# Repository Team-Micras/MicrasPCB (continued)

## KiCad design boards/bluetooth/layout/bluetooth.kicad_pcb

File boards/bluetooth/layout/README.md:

# Bluetooth module

The Micras Bluetooth module: a 16 x 25 mm, 2-layer, 0.79 mm board with an HM-19 Bluetooth Low
Energy module (TI CC2640R2F) and a vertical USB-C plug. It plugs into the main board's USB-C
receptacle U2 and stands upright behind the robot, and gives the firmware a wireless UART
(MicrasFirmware `bluetooth_design.md`: UART4, 115 200 8N1, no flow control). The main board it
plugs into is the v1 main board (MicrasPCB e34fb9a, `boards/main`); the current main board has no
USB-C receptacle, and its ESP32-C5 takes the radio's role.

The circuit is the MicrasBluetoothModule Altium design with two changes from the design review
(`hw_debug/schematic_review.md`): the plug's CC contacts carry the module's signature (M6), and
R4 pulls the HM-19's RESETB up (m17). Every part keeps its designator, and `micras-pcb previous
compare bluetooth` checks the netlist against that design's connectivity
([`previous/board.json`](../previous/board.json)) plus the changes in
[`changes.toml`](../changes.toml).

## Files

The board files are in `boards/bluetooth/` (this README sits in its `layout/` folder);
`spec/` is at the repository root.

| File | Contents |
|---|---|
| [`bluetooth.zen`](../bluetooth.zen) | the circuit (U1 HM-19, USB1 plug, R1-R4, C1, C2, D1, OP1), board stackup and rules |
| [`schematic/`](../schematic) | how the sheet is drawn (`micras-pcb sch`): the plug, and the HM-19 with its application circuit |
| [`erc.toml`](../erc.toml) | 3V3 and GND come from the main board through the plug (the PWR_FLAG role for ERC) |
| [`changes.toml`](../changes.toml) | connectivity changes against the previous revision: the CC signature (M6), the RESETB pull-up (m17) |
| [`test/`](../test) | `pcb test` bench of the circuit: HM-19 application circuit, LED current, USB-C signature, SBU and VBUS, RESETB |
| [`layout/`](.) | this folder: the KiCad project; the `.kicad_pcb` holds placement and routing; [`fixes.py`](fixes.py) is the pcbnew script that made the review fixes in it |
| [`previous/`](../previous) | the previous revision's snapshot and [`transfer_layout.py`](../previous/transfer_layout.py), which builds the layout from it |
| [`spec/bluetooth.toml`](../../../spec/bluetooth.toml) | mechanics: thickness, outline extents, plug and HM-19 positions, mating with the main board's U2 |

`tests/test_bluetooth.py` checks the board against its previous revision and the spec; the v1 main
board's tests (e34fb9a) check the joint with it.

## Circuit

The HM-19 application circuit of its datasheet (JNHuaMao "HM Bluetooth module datasheet" V107,
section 6.5); the docstring of [`bluetooth.zen`](../bluetooth.zen) cites each value.

| Part | Function |
|---|---|
| U1 | HM-19, VCC 2.1-3.7 V (V107 section 3), pins 9 and 10 on 3V3 |
| C1, C2 | 10 uF 35 V X5R and 100 nF 50 V X7R on 3V3 |
| R1 | 1 kOhm from HM-19 UART_TX (pin 2) to the plug's D- contacts (net `UART_TX`) |
| R2 | 1 kOhm from HM-19 UART_RX (pin 4) to the plug's D+ contacts (net `UART_RX`) |
| R3, D1 | the "System LED" output PIO1 (pin 15) through 680 Ohm to a blue 0603 LED: about 0.6 mA |
| R4 | 10 kOhm from RESETB (pin 11) to 3V3: the CC2640R2F's RESET_N has no internal pull-up (SWRS204C Table 7-1) |
| OP1 | open pad (bottom side) from PIO0 (pin 16, the key) to GND |
| USB1 | USB-C plug: 3V3 on SBU1/SBU2, UART on D+/D-, GND, CC1 and CC2 on D+ (the signature); VBUS open |

RTS, CTS, KEY (pin 8), PIO2 and PIO3 are open, as in the vendor schematic.

## Interface with the main board

The plug mates the main board's U2 (GT-USB-7010ASV) contact by contact. The plug joins both D+
contacts, both D- contacts and SBU1 with SBU2, and U2 joins them the same way, so the module works
either side up (the v1 main board's `tests/test_bluetooth.py` checks both orientations).

| Contacts | Module | Main board |
|---|---|---|
| SBU1, SBU2 (A8, B8) | `3V3`: U1 VCC, C1, C2 | `PERIPHERALS.SBU_PWR`: 3V3 through a switch and the PTC fuse F1 (KASML010), on while the main board reads the signature |
| D- (A7, B7) | `UART_TX`: R1 from HM-19 UART_TX | to MCU PA11 = UART4_RX |
| D+ (A6, B6) | `UART_RX`: R2 to HM-19 UART_RX | from MCU PA12 = UART4_TX |
| CC1, CC2 (A5, B5) | `UART_RX` (the signature) | R6, R7 5.1 kOhm Rd to GND, and the signature detector |
| GND, shell | `GND` | `GND` |
| VBUS (A4, A9, B4, B9) | open | `+5V`, the main board's USB power input |

The UART crosses correctly: the module transmits on D- into the MCU's receiver PA11, and receives
on D+ from PA12. With 1 kOhm in series per line on the module, the RC with the main board's
D+/D- capacitance (tens of pF) is tens of ns, against 8.68 us per bit at 115 200 baud.

### The signature (review M6)

USB Type-C reserves SBU for specified uses: a port leaves it open or pulls it down by at least
950 kOhm (Type-C R2.0 section 4.3 p139, Table 4-28 p236), and a full-featured cable wires it
through to a host's Alternate Mode or an audio accessory's microphone. So the main board may put
3V3 on SBU only when the module, and nothing else, is in its receptacle. The module identifies
itself on CC:

- **Module.** Both CC contacts are on its D+ contacts, so the signature shows either side up.
- **Main board.** D+ is the MCU's UART4 TX (PA12), which idles high once the firmware has started
  UART4 (at boot, `MX_UART4_Init`). Through the module it pulls the main board's CC contacts,
  each 5.1 kOhm Rd to GND, to the TX level: about 3.2 V, at least 2.87 V (STM32H725 DS13311
  Table 56: VOH >= VDD - 0.4 V; 3V3 >= 3.27 V). No Type-C partner makes that: across a sink's Rd
  a source makes at most 2.04 V (Table 4-36, vRd-Connect, +-10 % Rd; 2.18 V with +-20 %,
  Table 4-35), and cables and accessories only add Ra or Rd to GND. The main board's detector
  holds the peak of its CC1 through the UART's low bits and switches 3V3 onto SBU through F1
  when that peak rises above 2.26 V (two thirds of 3V3), and off again below 2.06 V. Its Rd stays
  as it is, so it is still a USB Type-C sink and its USB power input is unchanged.
- **Cost.** PA12 drives the two Rd in parallel, 2.55 kOhm (1.3 mA), while the module is plugged
  in. The module is unpowered until the firmware starts UART4, and loses power about 0.3 s after
  PA12 stops driving (an MCU reset held that long), as the detector's hold decays. Until the
  detector switches on (about 15 ms), PA12 also feeds a little current into the unpowered HM-19's
  UART_RX pin through R2.
- **Elsewhere.** Plugged into another USB-C port the module gets no supply (its VBUS is open and
  a host never drives SBU) and does nothing.

The main board's side is in its own pull request (the review fixes, #13).

## Board

2 copper layers, 35 um copper on a 0.7 mm FR-4 core (Dk 4.5), from the Altium layer stack; with
Zener's fixed 10 um solder mask a side it is 0.79 mm (Altium's 12.7 um resist makes 0.7954 mm),
ordered as JLCPCB's 0.8 mm board. Design rules: 0.1 mm clearance, 0.254 mm track, 0.6 / 0.3 mm
and 0.5 / 0.3 mm vias, 0.2 mm copper to edge, 0.02 mm solder mask expansion, the Altium JLCPCB
rule set; `rules/jlcpcb.kicad_dru` adds JLCPCB's limits on top. ENIG finish, black solder mask
and white silkscreen (Zener's 2-layer defaults, the owner's choice).

## Layout

The layout is the Altium MicrasBluetoothModule.PcbDoc's, in the same KiCad coordinates, built by
[`previous/transfer_layout.py`](../previous/transfer_layout.py) from KiCad's conversion of that PCB
(running the script again changes nothing), with the review fixes made on it by
[`layout/fixes.py`](fixes.py), which also sets the designators' size.

- **Top**: U1 near the top edge, with the antenna end of the module (the 7 mm above pad 1, V107
  6.6) 5.5 mm beyond the board's top edge; R2, R1, R3, D1, C2, C1 in a row below it, R4 above C2;
  USB1 at the bottom, in the narrow neck, with its CC pads joined to the adjacent D+ pads. RESETB
  runs from R4 under the module to U1 pad 11 from the inside of the pad row. GND pour.
- **Bottom**: OP1 at the top, the MICRAS logo in silkscreen, the routing that crosses the plug's
  rows. GND pour.
- The outline narrows from 16 mm to the plug's width towards the bottom edge.
- Resistors, capacitors and D1 use KiCad's generic footprints, each centred on its pads' positions
  in the Altium footprint: pad centres within 75 um of the Altium ones (the 0603 pad pitches
  differ). D1 carries KiCad's LED model scaled to the SMLD12BN1W's 0.55 mm height (ROHM
  datasheet p. 1). The teardrops of the Altium design are plain copper zones (priorities 100 and
  up), as on the main board: KiCad 10 orders zones by UUID and does not save a teardrop's UUID.
  They fill with a 0.1 mm minimum width, JLCPCB's minimum copper feature.
- The GND pours keep the Altium polygons' neck widths (copper narrower than 0.1 mm, 0.3 mm in the
  top pour around the plug, is not poured) and join pads solidly.
- The Edge.Cuts outline is the Altium one without its seven duplicated vertices (lines of 1-12 nm,
  which KiCad reads as a malformed, self-intersecting outline); the lines next to them meet within
  12 nm of where they did.
- Silkscreen: the reference designators are 0.5 mm high with a 0.125 mm stroke (the owner's
  choice), and so is the board's minimum (`bluetooth.zen`, `Silkscreen(minimum_text_height=0.5)`;
  the stroke in `rules/kicad-severities.toml`). JLCPCB recommends 1.0 mm text, so these may print
  less sharply; that is accepted.

## Differences from the Altium board

There is no Gerber output of the Altium design to compare with; against KiCad's conversion of the
PcbDoc, the board differs, besides the review fixes (the CC signature tracks, R4 and its tracks,
C2's designator beside C2), in:

| What | This board | Altium board | Why |
|---|---|---|---|
| Pour to board edge | 0.21 mm | 0.23 mm | the KiCad fill under `rules/jlcpcb.kicad_dru`: JLCPCB's 0.2 mm routed-edge clearance plus 10 um for the fill's arc approximation |
| R1-R3, C1, C2, D1 | KiCad's generic 0603 footprints: pads R 0.80 x 0.95, C 0.90 x 0.95, LED 0.875 x 0.95 mm, their centres within 75 um of the Altium ones; KiCad's silkscreen (no box around the parts, 6.2 mm2 less ink; D1's polarity mark an outline closed on the cathode side) | pads R 0.85 x 1.0, C 0.8 x 0.9, LED 0.8 x 0.8 mm; full boxes, a triangle on D1 | the stdlib generics' footprints |
| Passive 3D models | KiCad library models: R 0.45 mm tall, C 0.8 mm wide; D1 0.55 mm | R 0.56 mm, C 0.9 mm wide, D1 0.6 mm | KiCad's generic models (D1 scaled to its datasheet) |
| U1, USB1 courtyards | F.CrtYd rectangles 0.25 mm around the HM-19 body and pads, and around the plug's pads and legs | none (the HM-19 outline on User.15) | KiCad's courtyard overlap check |
| Teardrop cusps | thinner than 0.1 mm left out | drawn to a point | JLCPCB's 0.1 mm minimum copper feature |
| Solder mask thickness | 10 um a side | 12.7 um | Zener's stackup has no mask thickness setting |

## Mechanics

[`spec/bluetooth.toml`](../../../spec/bluetooth.toml) places the board frame on the plug centre and
exports `build/bluetooth/bluetooth_mech.json` (outline polygon, plug, HM-19, and where the board
sits in the robot). Mated, the module's component side faces the main board's rear edge at the USB
notch: the plug axis is on U2's axis (robot y = -1.75 mm) at 1.68 mm above the main board's top
surface (U2 drawing, CH), and the component side at robot x = -35.60 mm, 1.5 mm behind the notch
edge (x = -34.1 mm). That x follows from the receptacle drawing's mated dimensions (6.65 mm plug
shell, 1.85 mm Ref from the plug overmold to the receptacle face) and the plug's 8.65 mm height.

## Known faults

Every gate passes (the joint's checks, its signature detector `usb_c_sbu_open` and PA11's firmware
pull-up, are the v1 main board's, at e34fb9a). DRC and layout-check report one warning:

| Check (gate) | Fault | Requirement | Fix |
|---|---|---|---|
| `copper_sliver` (drc, warning) | 1: a teardrop outline overrunning its track on F.Cu; the teardrops are plain zones, which KiCad does not exempt from the sliver test | no copper sliver | trim the outline |

Requirements without a check, and why:

- The key (m17): the HM-19 datasheet puts the system key on pin 8 in its pin table and on PIO0
  (pin 16, where OP1 is) in its schematic and AT commands. Bridging OP1 for over 1000 ms in
  standby restores the factory settings, which the firmware's AT set-up relies on; `AT+SYSK0`
  makes the key only cancel, so send it when setting the module up. Which pin the fitted module
  uses needs a bench test.
- F1 against the module current (m17): F1 holds 50 mA at 85 C (KASML010), the HM-19 datasheet
  quotes 50 mA; no source gives the temperature inside the robot. At 50 mA the module still gets
  over 3.1 V: 3.27 V minimum, F1 up to 2 Ohm (0.1 V), the switch and contacts under 15 mV,
  against its 2.1 V minimum (V107 section 3).
- Hot plugging: C1 (10 uF) charges from the main board's 3V3 through F1 when the switch turns on
  and can dip 3V3; plug the module with the power off.
- Decoupling distance: the vendor schematic gives no distance for C1/C2.
- Mated depth: derived from the receptacle drawing, not measured.

## Open items

- [ ] Check every part's placement rotation in JLCPCB's assembly preview, then set
      `rotation_verified = true` in `parts/jlc.toml`.
- [ ] The HM-19 (LCSC C9900145630) has no stock at JLCPCB: source and consign it.
- [ ] Measure the mated position on the robot and correct `spec/bluetooth.toml` [mating].
- [ ] Bench test: the main board switches SBU on with the module in either orientation, and
      off with a USB host, a C-to-C cable and an audio adapter.

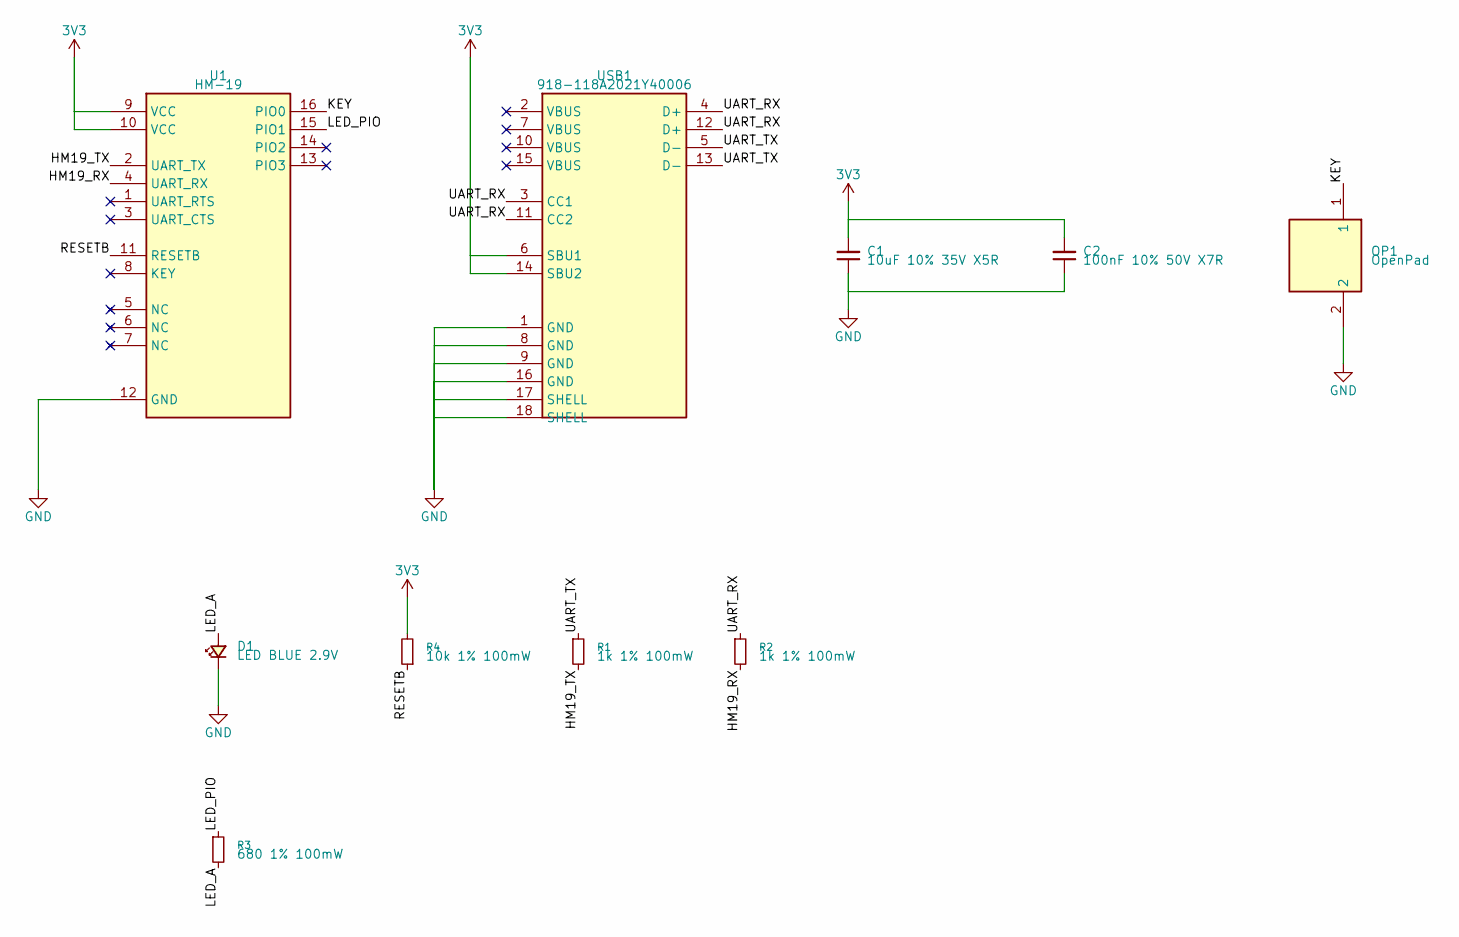
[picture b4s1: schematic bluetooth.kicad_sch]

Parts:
C1: 10uF 10% 35V X5R; C_0603_1608Metric
C2: 100nF 10% 50V X7R; C_0603_1608Metric
D1: LED BLUE 2.9V; LED_0603_1608Metric
OP1: OpenPad
R1, R2: 1k 1% 100mW; R_0603_1608Metric
R3: 680 1% 100mW; R_0603_1608Metric
R4: 10k 1% 100mW; R_0603_1608Metric
U1: HM-19
USB1: 918-118A2021Y40006; USB-C-SMD_918-118A2021Y40006

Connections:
3V3: C1.2, C2.2, R4.2, U1.9 (VCC), U1.10 (VCC), USB1.6 (SBU1), USB1.14 (SBU2)
GND: C1.1, C2.1, D1.1 (K), OP1.2, U1.12 (GND), USB1.1 (GND), USB1.8 (GND), USB1.9 (GND), USB1.16 (GND), USB1.17 (SHELL), USB1.18 (SHELL)
HM19_RX: R2.2, U1.4 (UART_RX)
HM19_TX: R1.2, U1.2 (UART_TX)
KEY: OP1.1, U1.16 (PIO0)
LED_A: D1.2 (A), R3.2
LED_PIO: R3.1, U1.15 (PIO1)
RESETB: R4.1, U1.11 (RESETB)
U1.NC_HM19_KEY: U1.8 (KEY)
U1.NC_HM19_PIO2: U1.14 (PIO2)
U1.NC_HM19_PIO3: U1.13 (PIO3)
U1.NC_HM19_UART_CTS: U1.3 (UART_CTS)
U1.NC_HM19_UART_RTS: U1.1 (UART_RTS)
UART_RX: R2.1, USB1.3 (CC1), USB1.4 (D+), USB1.11 (CC2), USB1.12 (D+)
UART_TX: R1.1, USB1.5 (D-), USB1.13 (D-)

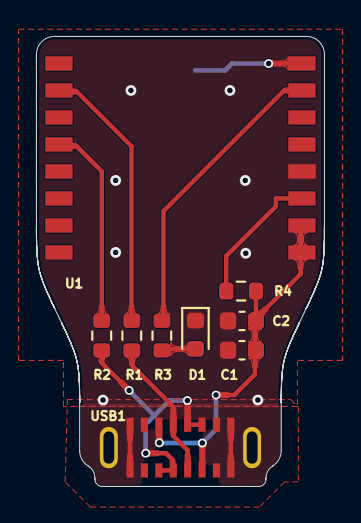
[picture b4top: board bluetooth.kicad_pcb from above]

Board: 2 copper layers, 16.0 x 25.0 mm, 10 parts (1 on the bottom side), 10 nets.

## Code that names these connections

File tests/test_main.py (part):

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    # SWD1 (main.zen): pad 1 NRST for the probe's RST wire, then the owner's clone ST-Link lead on
    # pads 2-5: 2 SWDIO, 3 GND, 4 SWCLK, 5 its 5 V pin. main.zen's docstring gives what each misplug
    # of the lead does; where the probe's 5 V lands must stay what it says.
    want = {1: d.net(MCU, "NRST"), 2: d.net(MCU, "PA13"), 3: "GND", 4: d.net(MCU, "PA14"), 5: "5V_IN"}
    got = {pad: d.net("SWD1", str(pad)) for pad in want}
    assert got == want, f"SWD1 pads {got}, expected {want}"
    lead = ["SWDIO", "GND", "SWCLK", "5V"]  # the lead's contacts in order
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
def test_no_usb_supply_and_no_5v_rail(d):
    # Research Design basis: the board has no USB receptacle and no 5 V rail; every supply comes
    # from J1. The one 5 V net is 5V_IN, a programmer's 5 V pin into VSYS through D17, which feeds
    # nothing else. The only USB nets are the ESP32-C5's data pair (GPIO13 D-, GPIO14 D+) to the bare
    # pads J3, with no VBUS (Esp.zen, USB pads).
    usb = sorted(n for n in d.nets() if re.search(r"USB|VBUS|5V", n.upper()) and n != "5V_IN")
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

def test_battery_divider_matches_the_firmware(d):
    # PC5 reads VBAT through the divider; the firmware's constant must be its ratio.
    tap = d.net(MCU, "PC5")
    vbat = d.net("IC8", "VM")
    up = d.two_terminal("resistor", vbat, tap)
    down = d.two_terminal("resistor", tap, "GND")
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# Firmware rules the hardware does not enforce (behaviour key -> words it must name).
FIRMWARE_RULES = {
    # a debug halt: the timers freeze and the drive enables drop (Drivers.zen, R49 covers reset only);
    # Motors_Enable (PD2) and Fan_Enable (PB12): one GPIOD and one GPIOB write
    "debug_halt": ["TIM1", "TIM8", "TIM14", "Motors_Enable", "Fan_Enable", "GPIOB_BSRR"],
    # the IMU shares SPI_SCK/SPI_MOSI with the encoders and decodes them as I2C while deselected
    "imu_interface": ["I2C_I3C_disable", "IF_CFG"],
    # Wall_Emitter_Set runs beside LED_ARGB and the encoder chip selects (Sensors.zen); the buzzer's
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    "emitter_slot_quiet": ["LED_ARGB", "SPI_SCK", "Encoder_Right_CSn", "Encoder_Left_CSn", "Buzzer"],
    # the STSPIN958's TOFF is low during the limiter's decay (DS14341 section 5.6.2, Figure 14), read
    # in step with the PWM; it leaves the decay only on a PWM1 low edge (section 5.6.2.2)
    "fan_toff": ["low while the limiter decays", "TIM14 has no DMA request", "GPIOB_IDR"],
    "fan_pwm": ["1 - 280 ns x fPWM", "88.8 %"],
    # the overcurrent trip is per MOSFET, so a 400 kHz stall below it persists (DS14341 section 5.7)
    "fan_start": ["per MOSFET", "12.8-28 A"],
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    # the IMU and encoder bus on SPI2 and its DMA requests (sensor_bus)
    "sensor_bus_dma": ["SPI2", "39", "40"],
    # Button's EXTI line has its interrupt to itself (button)
    "button_input": ["PC4", "EXTI4"],
    # the LEDs' timer and DMA request, the buzzer's timer (leds, buzzer; RM0468 Table 118)
    "led_timer": ["TIM15", "tim15_up", "106", "MOE"],
    "buzzer_timer": ["TIM17", "MOE"],
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        "WR_DONE (CMD7)",
        "CMD8",
        # ESP_Flow's EXTI11 shares the EXTI15_10 interrupt with Fan_Enable's fault line (EXTI12)
        "EXTI11 on PA11",
        "EXTI15_10",
    ],
    # the C5 recovers the link after the MCU resets, closing buffers with commands, not ESP_CSn
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    # Without an HSE crystal the H7 runs on its HSI, +-1 % over temperature (DS13311 Rev 5 Table 40),
    # which scales the gyro's yaw integral; the firmware then measures it against the ESP32-C5's
    # crystal over the link (firmware_changes.toml timebase), and the C5 stays on in contest mode.
    osc = [d.net(MCU, pin) for pin in ("PH0-OSC_IN", "PH1-OSC_OUT")]
    assert all(osc), f"PH0/PH1 not found on {MCU}"
    clocked = sorted(r for net in osc for r in d.refs_on(net) if d.kind(r) in CLOCK_KINDS)
    if clocked:
        pytest.skip(f"the MCU has its own clock reference: {clocked}")
    words = ["HSI", "ESP_CSn", "crystal", "loop_time", "contest"]
    text = FW["behaviour"].get("timebase", "")
    missing = [w for w in words if w not in text]
    assert not missing, f"no crystal on PH0/PH1 ({osc}): behaviour.timebase must name {missing}"


def test_every_free_running_timer_output_has_low_output_speed():
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
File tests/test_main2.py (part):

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    if vsys not in _reach(edges, vbat):
        problems.append(f"{vbat} does not reach VSYS")
    if vsys not in _reach(edges, v5):
        problems.append(f"{v5} (J2 pin 2) does not reach VSYS")
    if d.net("SWD1", "4") != v5:
        problems.append(f"SWD1 pad 4 is on {d.net('SWD1', '4')}, not J2 pin 2's {v5}")
    for start in (vbat, vsys):
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def test_swd_header_follows_the_clone_st_link_order(d):
    # The owner's clone ST-Link lead (main2.zen): pads 1 SWDIO, 2 GND, 3 SWCLK, 4 its 5 V pin. Plugged
    # turned round, or shifted one pad either way, the probe's 5 V pin never lands on GND.
    want = {1: d.net(MCU, "PA13"), 2: "GND", 3: d.net(MCU, "PA14"), 4: "5V_IN"}
    got = {pad: d.net("SWD1", str(pad)) for pad in want}
    assert got == want, f"SWD1 pads {got}, expected {want}"
    probe_5v = 4  # the lead's pins in the same order: 1 SWDIO, 2 GND, 3 SWCLK, 4 5V
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
def test_no_usb_and_no_5v_rail(d):
    # Research Design basis: the board has no USB and no 5 V rail; every supply comes from J1. The
    # one 5 V net is 5V_IN, a programmer's 5 V pin into VSYS through D17, which feeds nothing else.
    usb = sorted(n for n in d.nets() if re.search(r"USB|VBUS|5V", n.upper()) and n != "5V_IN")
    assert not usb, f"USB or 5 V nets on the board: {usb}"
    on_5v = sorted(r for r, _, _ in d.on("5V_IN"))
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

def test_battery_divider_matches_the_firmware(d):
    # PC5 reads VBAT through the divider; the firmware's constant must be its ratio.
    tap = d.net(MCU, "PC5")
    vbat = d.net("IC8", "VM")
    up = d.two_terminal("resistor", vbat, tap)
    down = d.two_terminal("resistor", tap, "GND")
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# Firmware rules the hardware does not enforce (behaviour key -> words it must name).
FIRMWARE_RULES = {
    # a debug halt: the timers freeze and the drive enables drop (Drivers.zen, R49 covers reset only);
    # Motors_Enable (PB8) and Fan_Enable (PB12) are both port B pins: one GPIOB write
    "debug_halt": ["TIM1", "TIM8", "TIM14", "Motors_Enable", "Fan_Enable", "GPIOB_BSRR"],
    # the IMU shares SPI_SCK/SPI_MOSI with the encoders and decodes them as I2C while deselected
    "imu_interface": ["I2C_I3C_disable", "IF_CFG"],
    # Wall_Emitter_Set runs beside LED_ARGB and the encoder chip selects (Sensors.zen)
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    # the IMU and encoder bus on SPI2 and its DMA requests (sensor_bus)
    "sensor_bus_dma": ["SPI2", "39", "40"],
    # Button's EXTI line has its interrupt to itself (button)
    "button_input": ["PA3", "EXTI3"],
    # the LEDs' timer and DMA request, the buzzer's timer (leds, buzzer; RM0468 Table 118)
    "led_timer": ["TIM15", "tim15_up", "106", "MOE"],
    "buzzer_timer": ["TIM17", "MOE"],
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        "WR_DONE (CMD7)",
        "CMD8",
        # ESP_Flow's EXTI11 shares the EXTI15_10 interrupt with Fan_Enable's fault line (EXTI12)
        "EXTI11 on PA11",
        "EXTI15_10",
    ],
    # the C5 recovers the link after the MCU resets, closing buffers with commands, not ESP_CSn
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
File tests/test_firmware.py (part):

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        slot = [r for r in d.refs_on(cs) if r.startswith("EC")]
        if not slot or d.net(slot[0], "7") != a or d.net(slot[0], "8") != _net(d, f"Encoder_{side}_ABI_B"):
            problems.append(f"Encoder_{side}_CSn and Encoder_{side}_ABI_A/B are not on one encoder slot")
    expect("Motors_Enable", "IC5", "ENA", "the firmware enables the bridges on this pin")
    for n in range(4):
        # emitter n's switch and receiver n in the same wall sensor
        gate_nets = _through_series_capacitors(d, _reach(d, _net(d, f"Wall_Sensor_PWM_{n}")))
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

# ADC inputs of the free and analog pins (DS13311 Rev 5 Table 8, VFQFPN68).
ADC_PINS = {"PA4", "PA5", "PA6", "PC4", "PB1", "PC0", "PC1"}


def test_battery_voltage_is_measurable(d):
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    over = []
    for w, r, i in _emitters(d):
        fet = [q for q in d.refs("AO3400A") if d.net(q, "D") == d.net(w, "LED_K")]
        # DC-coupled: the gate reaches the MCU pin through resistors only (no series capacitor)
        dc_coupled = bool(_reach(d, d.net(fet[0], "G")) & set(_gpio_nets(d).values()))
        if dc_coupled and i > SFH4550_IF_DC:
            over.append(f"{w}: {i * 1e3:.0f} mA DC through {r} with {fet[0]}'s gate held high, above 100 mA")
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
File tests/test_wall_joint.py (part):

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# Each joint's selector on its TIM3 channel and its receiver on its ADC line
# (boards/main/firmware_changes.toml, emitters; boards/main/test/test_sensors.zen CHANNELS).
CHANNELS = {
    "W1": ("PC9", "Wall_Sensor_0"),
    "W2": ("PB0", "Wall_Sensor_1"),
    "W3": ("PB5", "Wall_Sensor_2"),
    "W4": ("PB4", "Wall_Sensor_3"),
}
SINK_FET = "Q9"
R_LOAD = 1e3  # the receiver's load at the ADC (boards/main/Sensors.zen, Receiver n)
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
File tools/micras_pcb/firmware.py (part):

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
    [[change]]
    id = "C1"                                  # required, unique: the board change it follows
    summary = "Battery voltage on PA5"         # required
    pins = { "PA5" = { signal = "ADCx_INP19", label = "Battery_Voltage" } }   # pins set or replaced
    battery = { channel = "pin", divider = 4.7037 }                          # sections merged key by key

Sections other than pins (supply, battery, drive, adc, behaviour) merge key by key into the
contract. `adc` holds the ADC numbers a board circuit relies on (a minimum sampling time), so a
test can compute with them.
`behaviour` names what the firmware must do differently where no pin or number captures it (a
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    return BOARDS / board / "firmware_changes.toml"


CHANGE_SECTIONS = ("pins", "supply", "battery", "drive", "adc", "behaviour")


def load_changes(board: str = "main", path: Path | None = None) -> list[dict]:
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

def _pin_name(key: str) -> str:
    """'PA13(JTMS/SWDIO)' -> 'PA13'; 'PC14-OSC32_IN' stays (the symbol's pin name)."""
    return key.split("(", 1)[0]


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
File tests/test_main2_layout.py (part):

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    return centre - a.width / 2 - b.width / 2


# The STM32's supplies on In2.Cu (boards/main2/layout/route.py, planes()): its 3V3_D and VCORE pins
# alternate round all four of its sides, and nest there as islands rather than ring it as tracks
# (owner, 2026-10-18). They stay within MCU_REACH of its centre.
MCU_ISLANDS = {"3V3_D", "VCORE"}
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FAST_GAP = 0.45  # mm
ESCAPE_REACH = 1.0  # mm
CLOSE_NEIGHBOURS = {
    # Fan_PWM's pin (PA7, pin 26) sits between ADC pins 23-28 (Wall_Sensor_0, Wall_Sensor_2,
    # Wall_Sensor_1, Battery_Voltage): its escape runs with theirs until a via site frees it
    ("Battery_Voltage", "Fan_PWM"): 6.1,
    ("VDDA", "Fan_PWM"): 0.3,
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
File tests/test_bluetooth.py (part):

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@needs_pcb
@pytest.mark.parametrize("orientation", ["normal", "flipped"])
def test_uart_crosses_to_the_firmware_uart(orientation):
    # HM-19 UART_TX must reach the MCU pin the firmware uses as UART RX, and UART_RX the TX pin
    # (boards/main/firmware.toml: PA11 UART4_RX, PA12 UART4_TX).
    bt, main, fw = design("bluetooth"), design("main"), firmware.load("main")
    want = {"UART_TX": "_RX", "UART_RX": "_TX"}
    problems = []
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@needs_kicad
@needs_pcb
def test_uart_rx_is_held_with_the_module_unplugged():
    # With the module unplugged the MCU's UART RX input (PA11) ends at an open contact, and an input
    # without a pull floats, so the receiver collects noise bytes (hw_debug/schematic_review.md m17,
    # review_research/04 section 9: PA11 has no GPIO_PuPd). The firmware's pin map or the board
    # must hold it high (the UART idle level). The firmware's pin map counts with the changes the
    # board declares for it (boards/main/firmware_changes.toml).
    main = design("main")
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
